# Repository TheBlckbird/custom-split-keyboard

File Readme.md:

⚠️ **Disclaimer! WIP** ⚠️ This PCB won't work in its current form!

# Custom Split Keyboard

The PCBs for my custom split keyboard are available in this repository.

The PCB is made for hotswap switches compatible with the Choc v1 or v2 footprint.
The first unique part about this is that it only uses one MCU and connects the two sides with a miniHDMI cable.
The other unique thing is that it has arrow keys.

## Layout

| **left**  | **right**  |
|-----------|------------|
|  |  |

## Roadmap for future versions

- [ ] Rethink the key layout
    - [ ] Are the arrow keys really needed?
- [ ] Wireless (partially or completely using the nice!nano)
- [ ] LEDs for the wired version
- [ ] Display for the wireless version (nice!view or e-paper)

## License

This project is licensed under [MIT](/LICENSE)

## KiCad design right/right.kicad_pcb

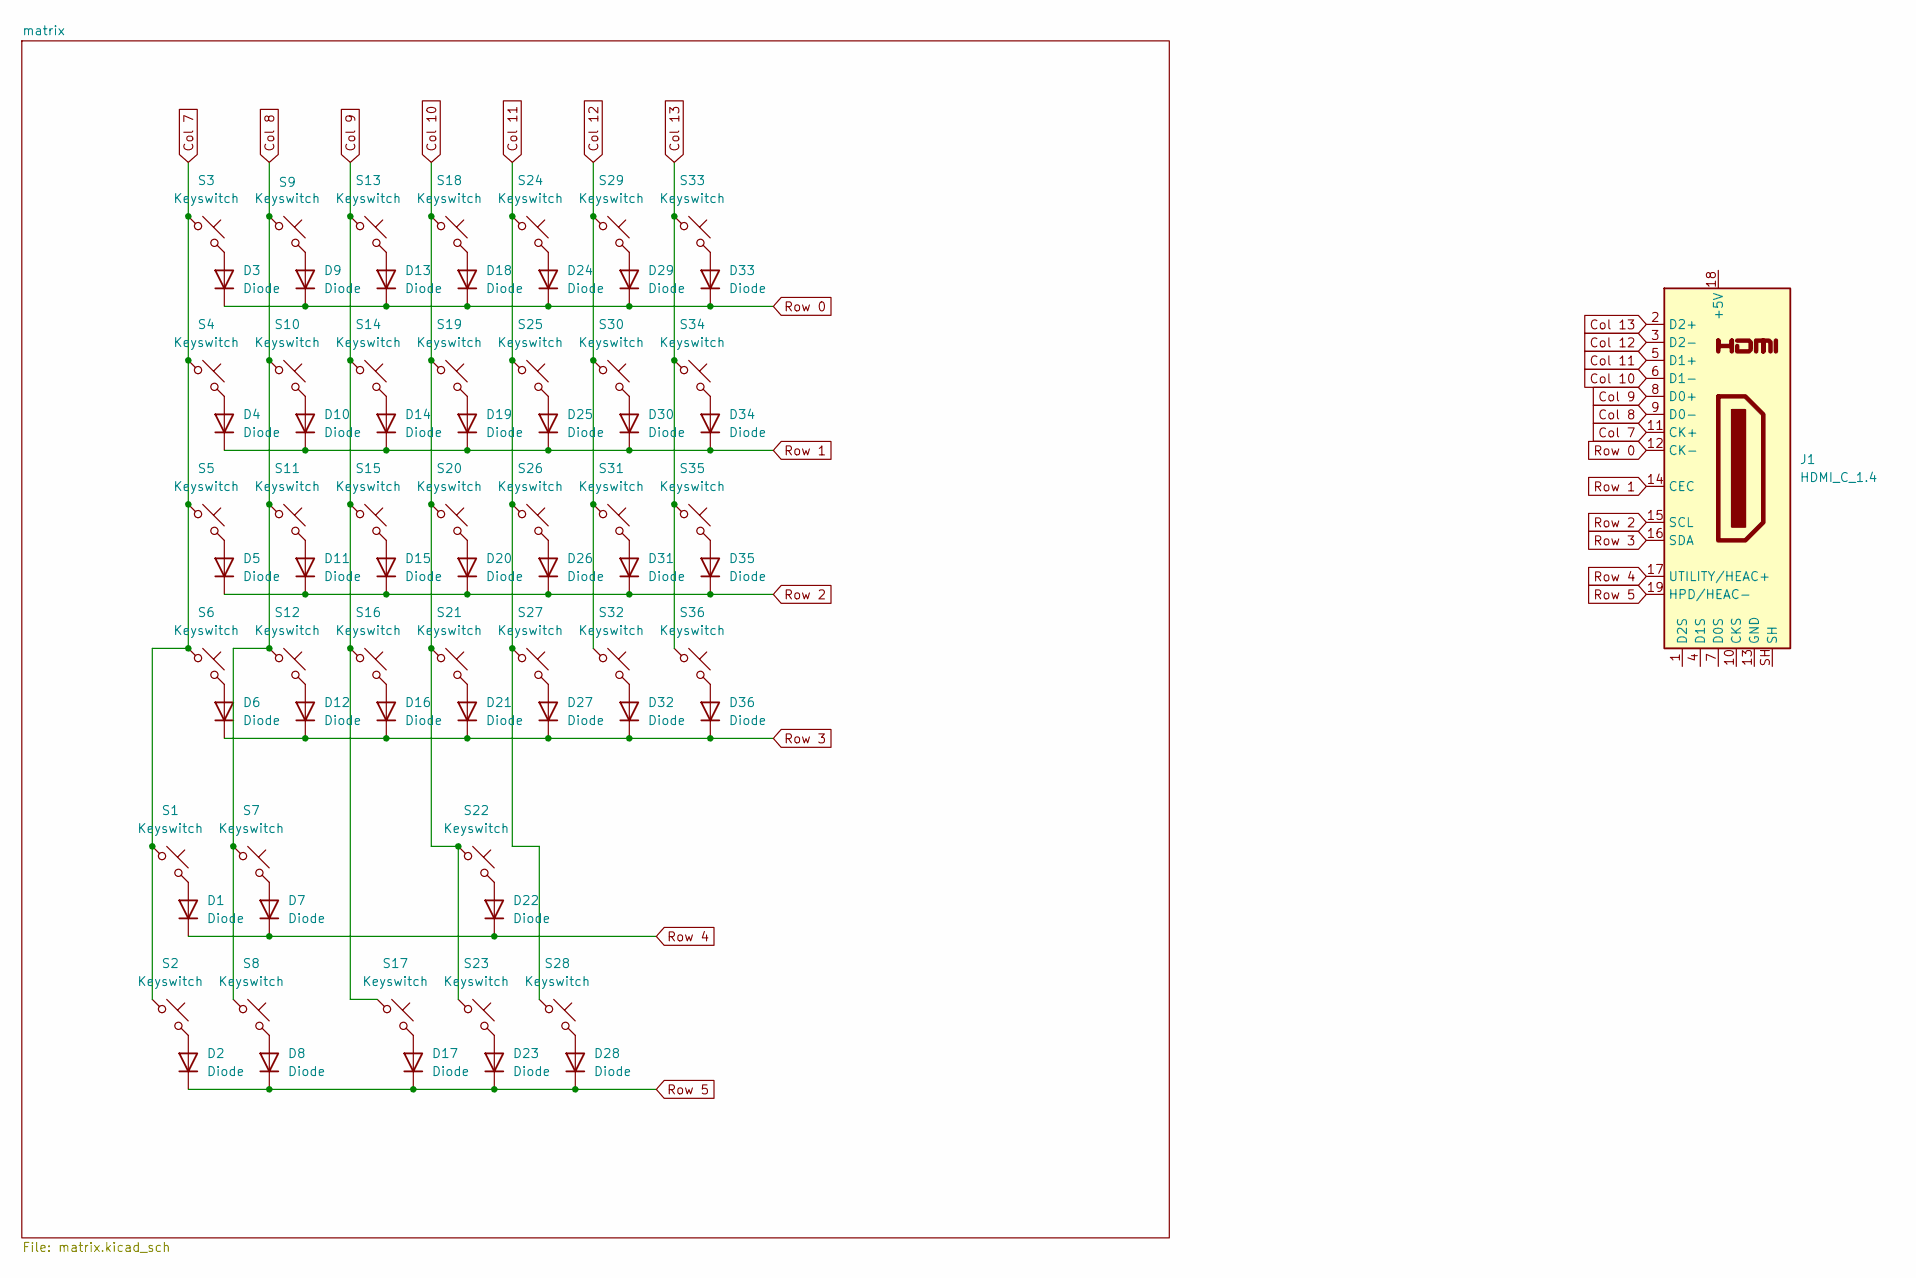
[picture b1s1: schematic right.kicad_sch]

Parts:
D1, D2, D3, D4, D5, D6, D7, D8, D9, D10, D11, D12, D13, D14, D15, D16, D17, D18, D19, D20, D21, D22, D23, D24, D25, D26, D27, D28, D29, D30, D31, D32, D33, D34, D35, D36: Diode; Diode_DO-35
J1: HDMI_C_1.4; 685119136923
S1, S3, S4, S5, S6, S7, S9, S10, S11, S12, S13, S14, S15, S16, S17, S18, S19, S20, S21, S22, S23, S24, S25, S26, S27, S28, S29, S30, S31, S32, S33, S34, S35, S36: Keyswitch; Hotswap_Choc_V1V2_1.00u
S2, S8: Keyswitch; Hotswap_Choc_V1V2_1.50u_90deg

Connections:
Col 7: J1.11 (CK+), S1.1, S2.1, S3.1, S4.1, S5.1, S6.1
Col 8: J1.9 (D0-), S7.1, S8.1, S9.1, S10.1, S11.1, S12.1
Col 9: J1.8 (D0+), S13.1, S14.1, S15.1, S16.1, S17.1
Col 10: J1.6 (D1-), S18.1, S19.1, S20.1, S21.1, S22.1, S23.1
Col 11: J1.5 (D1+), S24.1, S25.1, S26.1, S27.1, S28.1
Col 12: J1.3 (D2-), S29.1, S30.1, S31.1, S32.1
Col 13: J1.2 (D2+), S33.1, S34.1, S35.1, S36.1
unnamed: D1.2 (A), S1.2
unnamed: D2.2 (A), S2.2
unnamed: D3.2 (A), S3.2
unnamed: D4.2 (A), S4.2
unnamed: D5.2 (A), S5.2
unnamed: D6.2 (A), S6.2
unnamed: D7.2 (A), S7.2
unnamed: D8.2 (A), S8.2
unnamed: D9.2 (A), S9.2
unnamed: D10.2 (A), S10.2
unnamed: D11.2 (A), S11.2
unnamed: D12.2 (A), S12.2
unnamed: D13.2 (A), S13.2
unnamed: D14.2 (A), S14.2
unnamed: D15.2 (A), S15.2
unnamed: D16.2 (A), S16.2
unnamed: D17.2 (A), S17.2
unnamed: D18.2 (A), S18.2
unnamed: D19.2 (A), S19.2
unnamed: D20.2 (A), S20.2
unnamed: D21.2 (A), S21.2
unnamed: D22.2 (A), S22.2
unnamed: D23.2 (A), S23.2
unnamed: D24.2 (A), S24.2
unnamed: D25.2 (A), S25.2
unnamed: D26.2 (A), S26.2
unnamed: D27.2 (A), S27.2
unnamed: D28.2 (A), S28.2
unnamed: D29.2 (A), S29.2
unnamed: D30.2 (A), S30.2
unnamed: D31.2 (A), S31.2
unnamed: D32.2 (A), S32.2
unnamed: D33.2 (A), S33.2
unnamed: D34.2 (A), S34.2
unnamed: D35.2 (A), S35.2
unnamed: D36.2 (A), S36.2
Row 0: D3.1 (K), D9.1 (K), D13.1 (K), D18.1 (K), D24.1 (K), D29.1 (K), D33.1 (K), J1.12 (CK-)
Row 1: D4.1 (K), D10.1 (K), D14.1 (K), D19.1 (K), D25.1 (K), D30.1 (K), D34.1 (K), J1.14 (CEC)
Row 2: D5.1 (K), D11.1 (K), D15.1 (K), D20.1 (K), D26.1 (K), D31.1 (K), D35.1 (K), J1.15 (SCL)
Row 3: D6.1 (K), D12.1 (K), D16.1 (K), D21.1 (K), D27.1 (K), D32.1 (K), D36.1 (K), J1.16 (SDA)
Row 4: D1.1 (K), D7.1 (K), D22.1 (K), J1.17 (UTILITY/HEAC+)
Row 5: D2.1 (K), D8.1 (K), D17.1 (K), D23.1 (K), D28.1 (K), J1.19 (HPD/HEAC-)

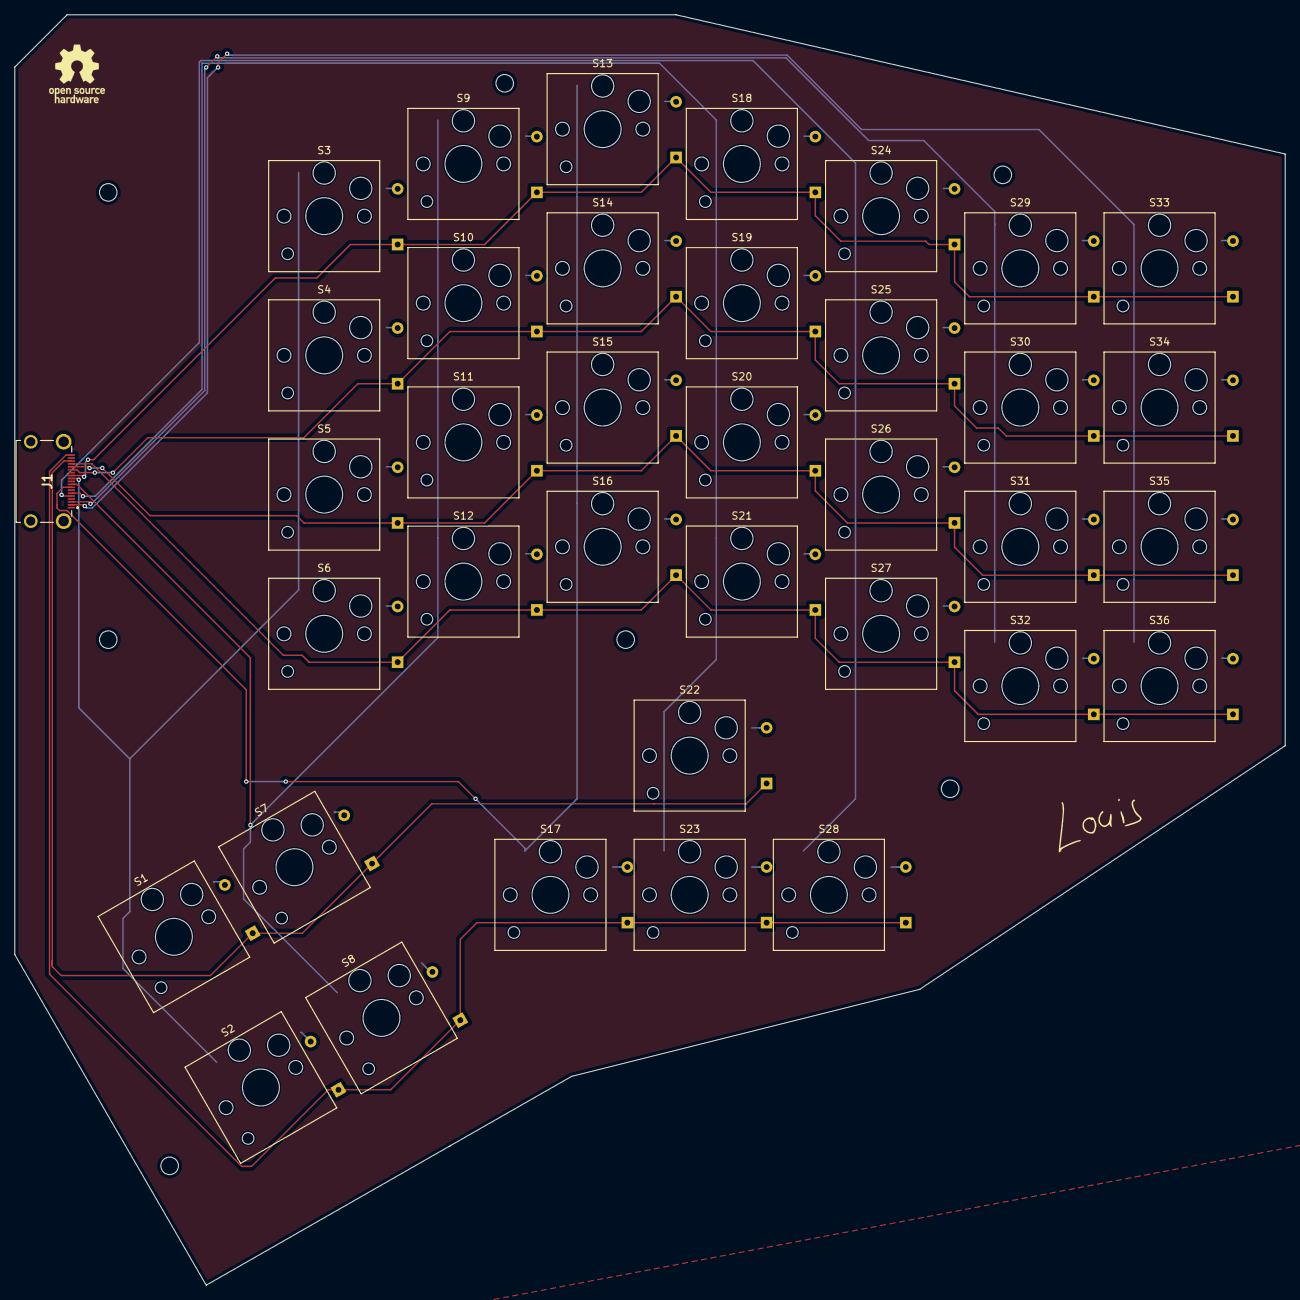
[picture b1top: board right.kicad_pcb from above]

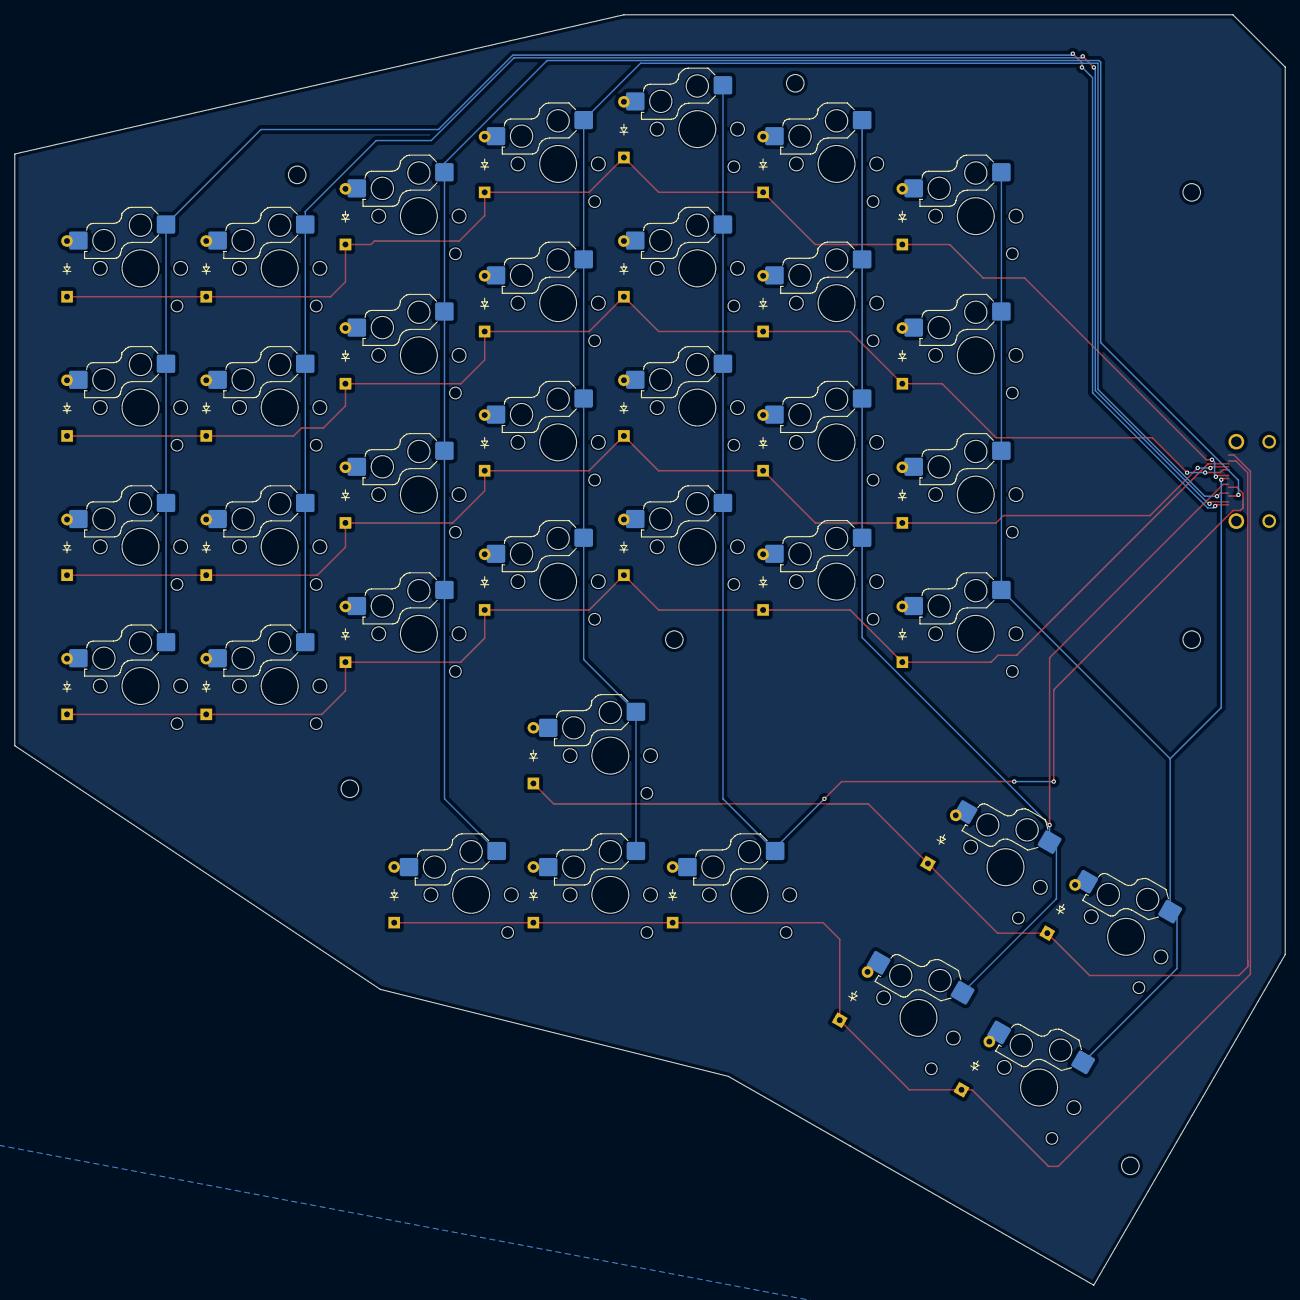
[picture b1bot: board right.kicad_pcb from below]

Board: 2 copper layers, 173.8 x 173.8 mm, 73 parts (36 on the bottom side), 49 nets.

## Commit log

2025-10-20 Initial commit and add left and right and layout
2025-10-20 Backlink to CADLAB.io has been added.
2025-10-20 Fix issues from update to KiCad 9
2025-10-22 Add OSHW logo
